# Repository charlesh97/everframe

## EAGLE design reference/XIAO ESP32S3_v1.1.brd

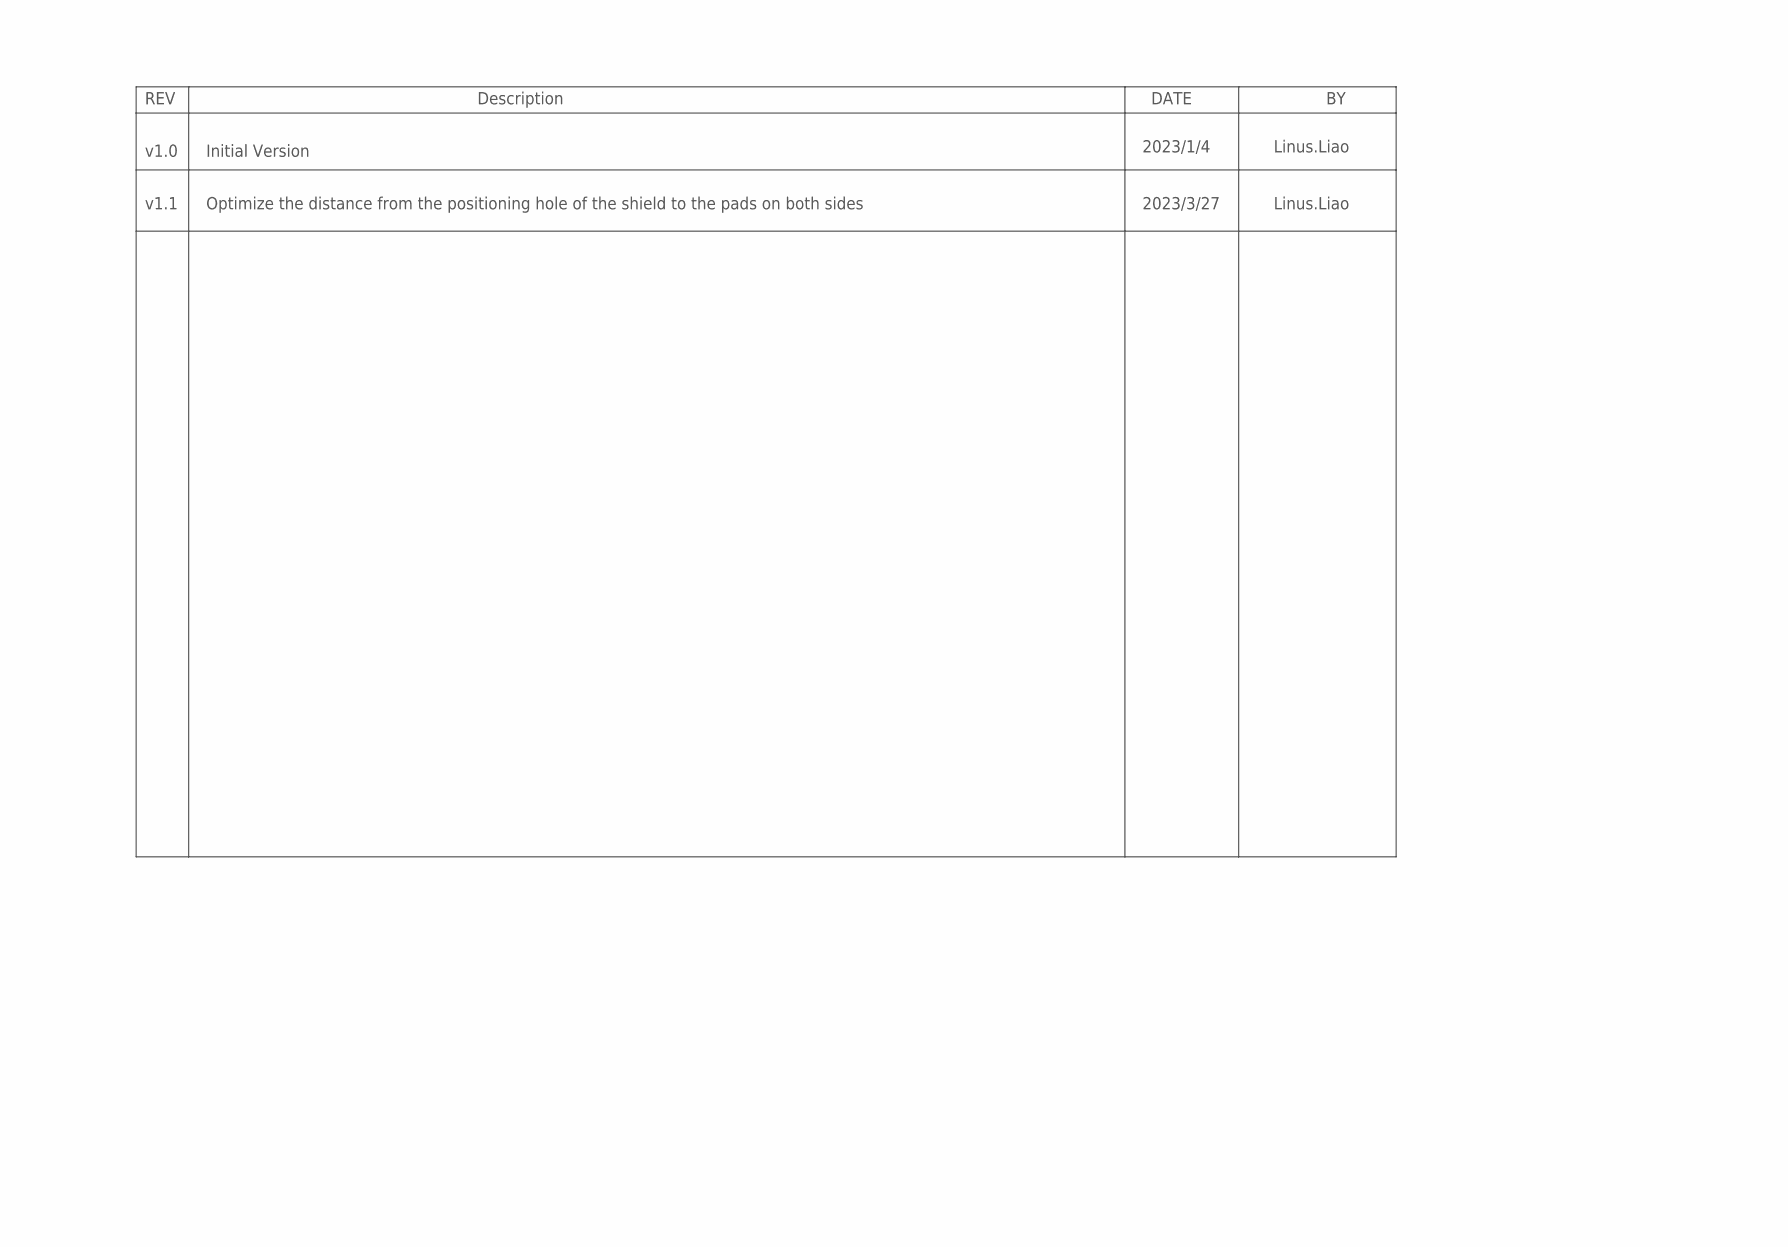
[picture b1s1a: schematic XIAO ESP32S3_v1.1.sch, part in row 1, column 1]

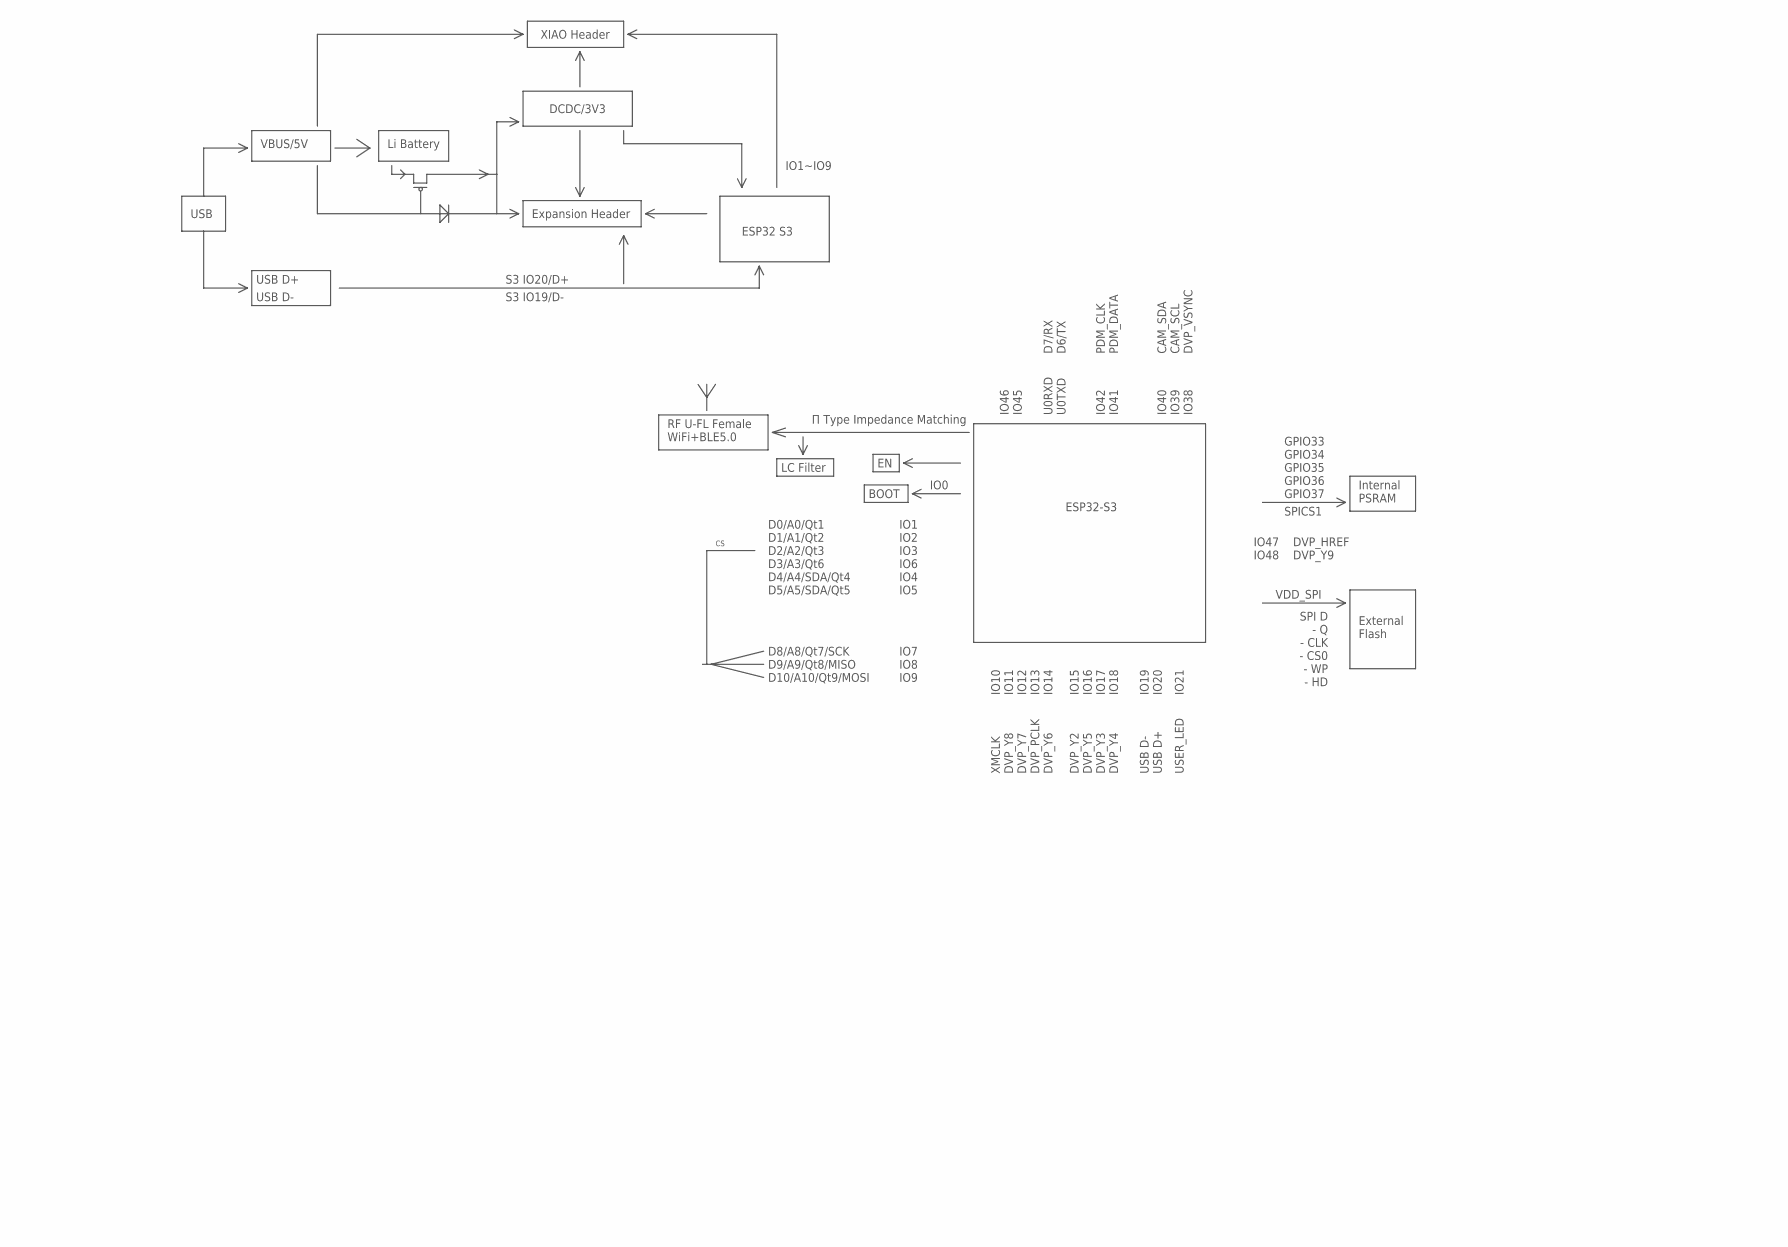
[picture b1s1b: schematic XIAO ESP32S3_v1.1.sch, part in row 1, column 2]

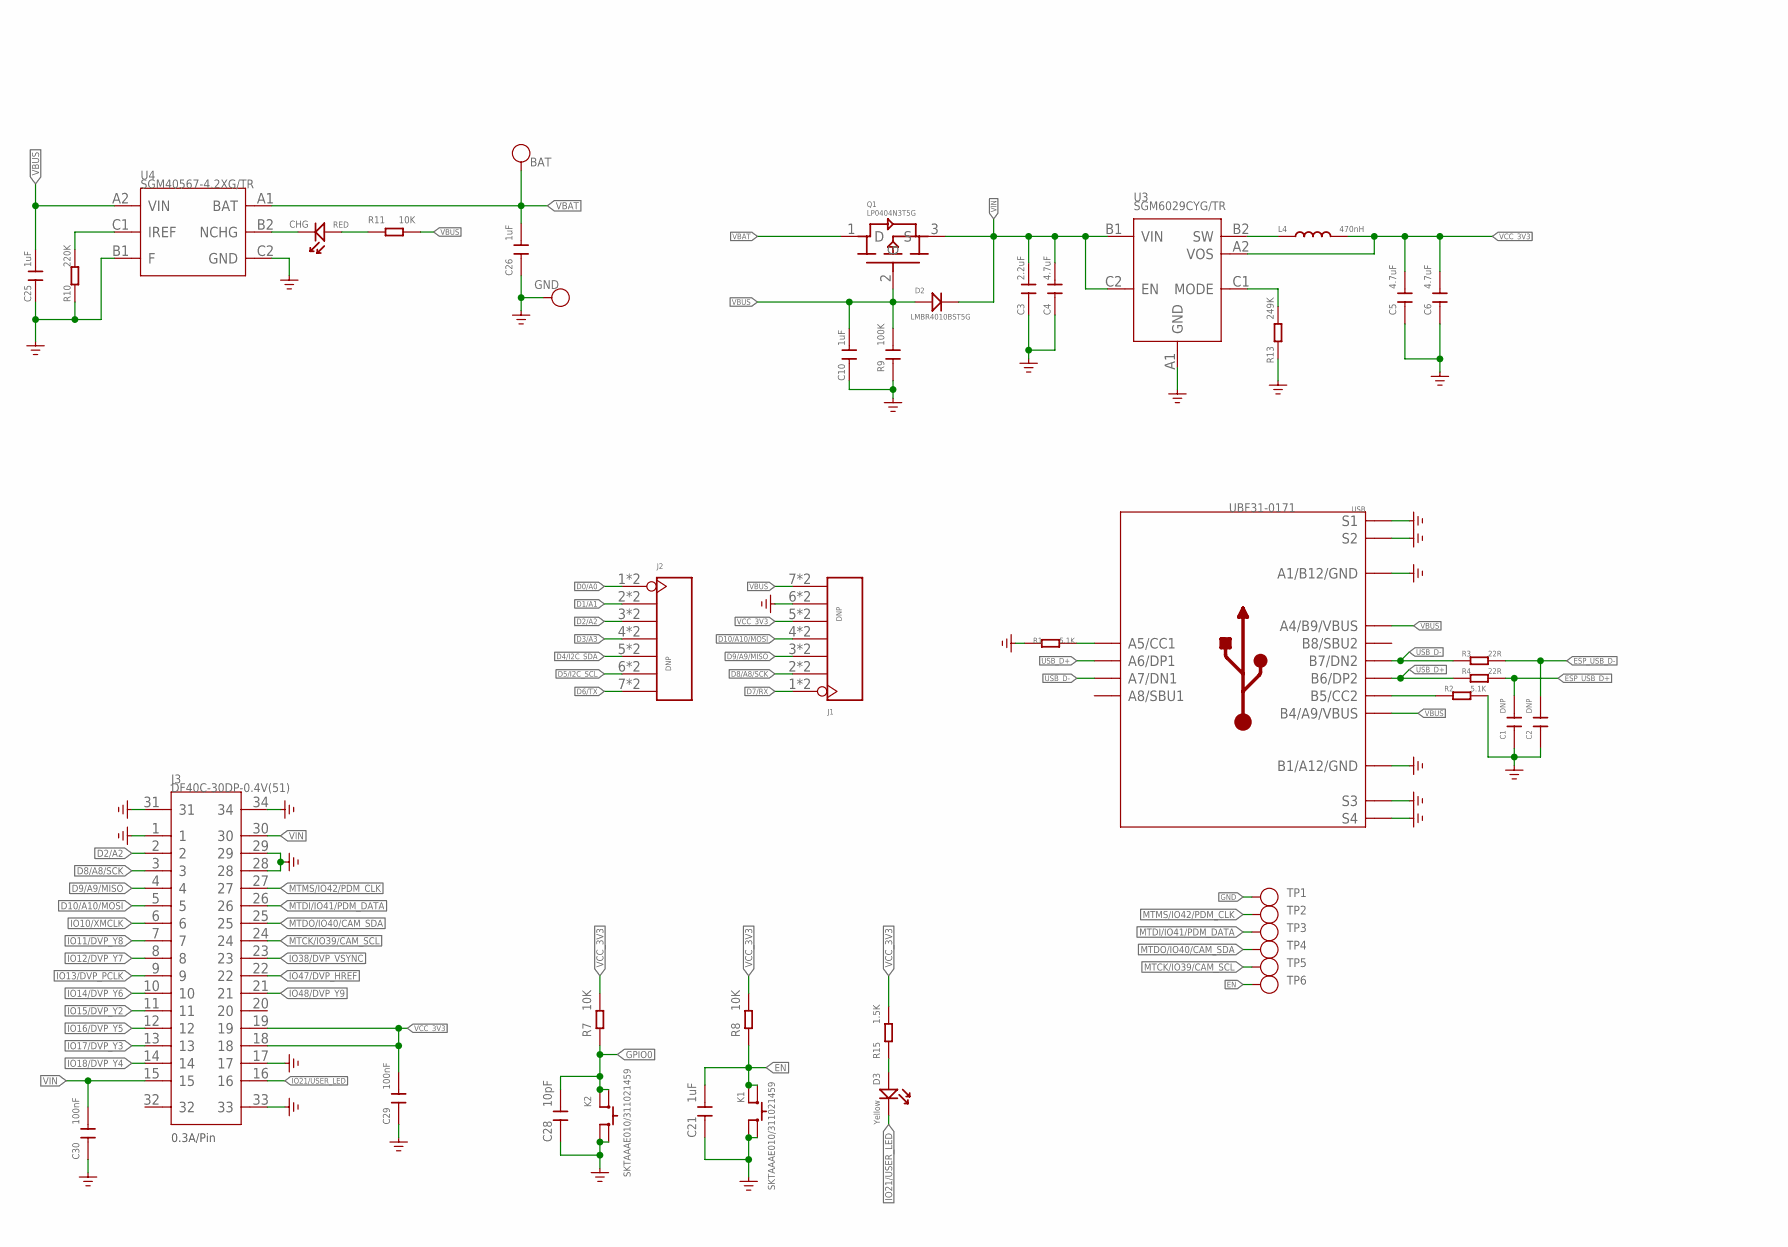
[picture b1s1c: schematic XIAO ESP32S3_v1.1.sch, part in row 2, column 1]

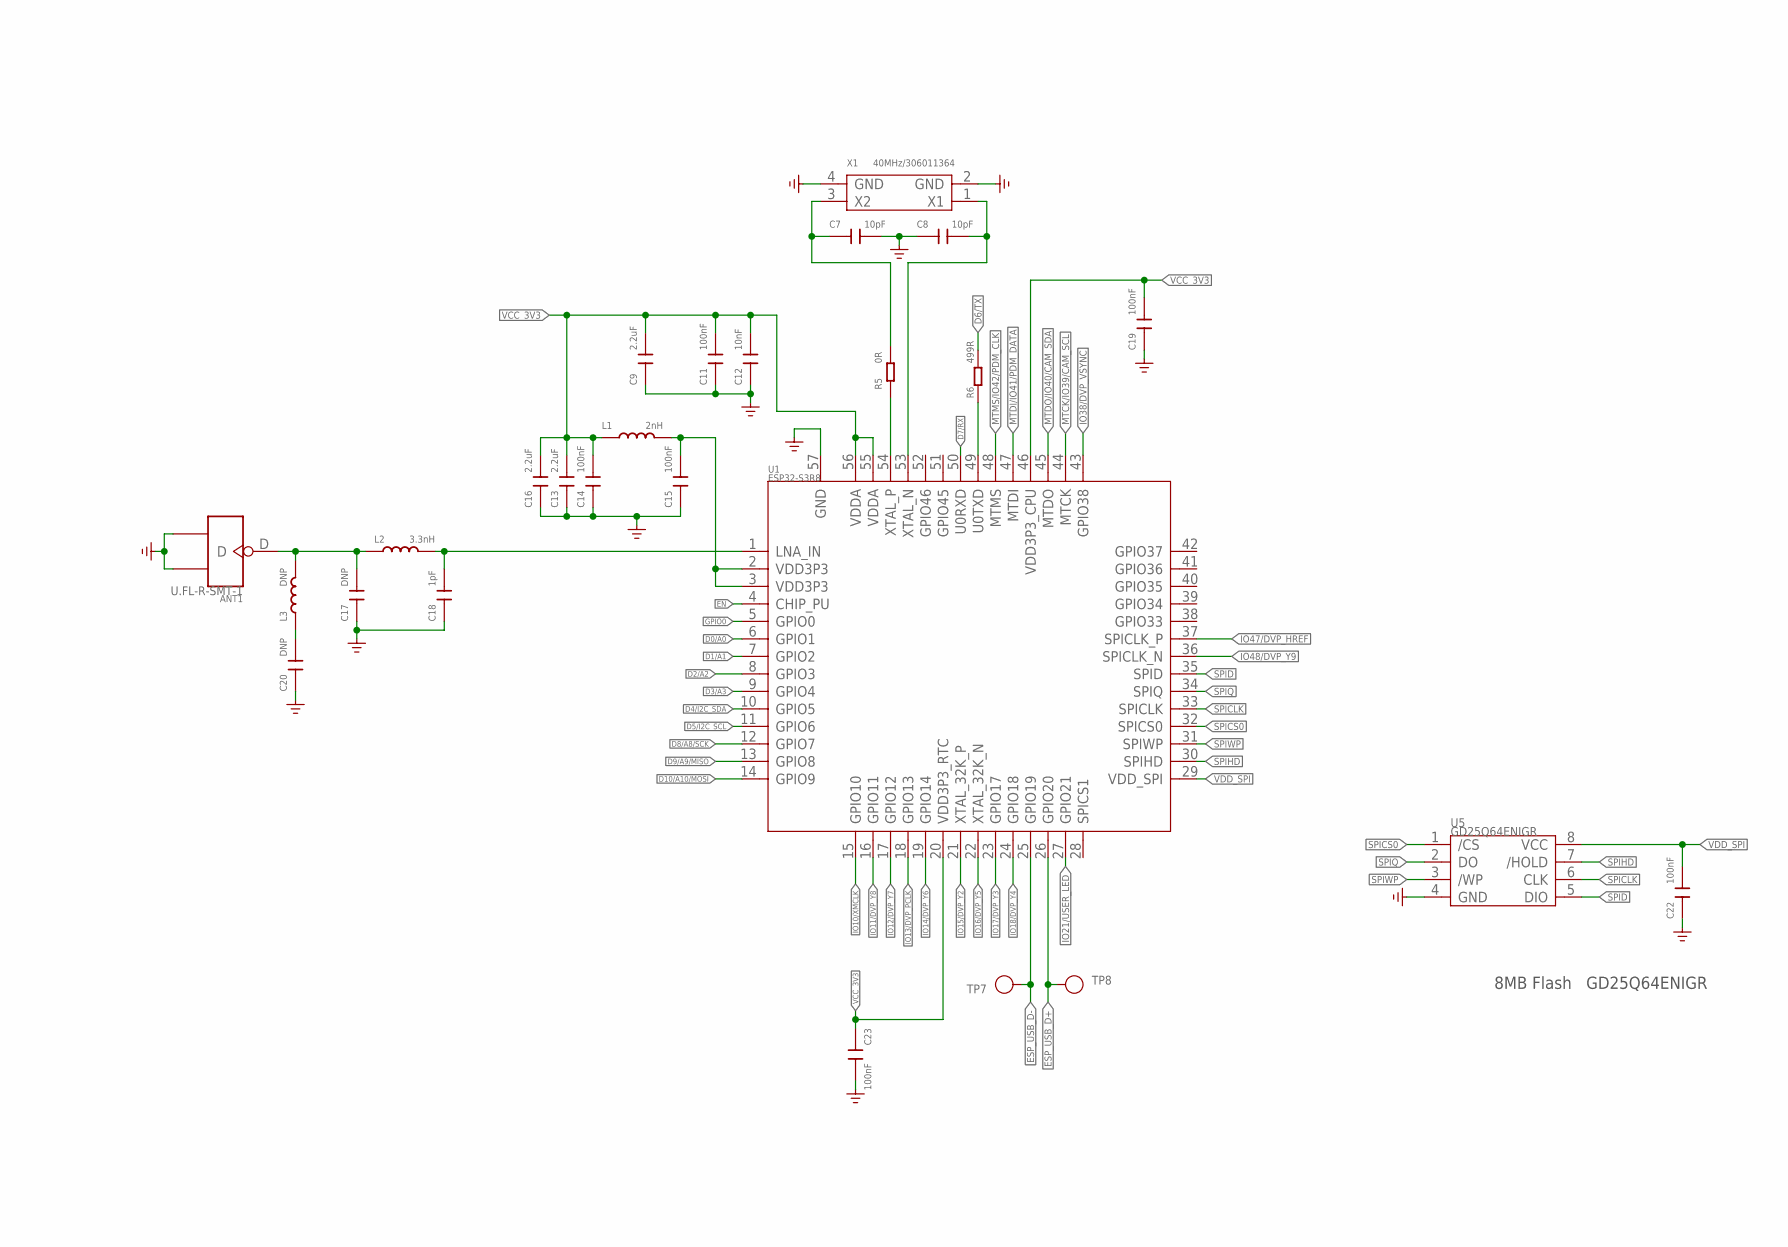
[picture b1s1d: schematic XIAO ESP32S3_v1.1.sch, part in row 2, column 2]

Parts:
ANT1: U.FL-R-SMT-1; U-FL3P-SMD-2.6X2.6X1.0MM
BAT: VBAT; TP-80X40MIL
C1, C2, C17, C20: DNP; C0201
C3, C9, C13, C16: 2.2uF; C0201
C4, C5, C6: 4.7uF; C0201
C7, C8, C28: 10pF; C0201
C10, C21, C25, C26: 1uF; C0201
C11, C14, C15, C19, C22, C23, C29, C30: 100nF; C0201
C12: 10nF; C0201
C18: 1pF; C0201
CHG: RED; LED-0402
D2: LMBR4010BST5G; DFN1006-2L
D3: Yellow; LED-0402
GND: GND; TP-80X40MIL
J1, J2: DNP; H7-HALF-HOLE-2.54
J3: DF40C-30DP-0.4V(51); BTB30-0.4-7.52X2.97X1.14
K1, K2: SKTAAAE010/311021459; SW4-SMD-2.8-2.6X1.6X0.53MM
L1: 2nH; L0201
L2: 3.3nH; L0201
L3: DNP; L0201
L4: 470nH; L0603
Q1: LP0404N3T5G; PMOS_1.0*0.6*0.35MM
R1, R2: 5.1K; R0201
R3, R4: 22R; R0201
R5: 0R; R0201
R6: 499R; R0201
R7, R8, R11: 10K; R0201
R9: 100K; C0201
R10: 220K; R0201
R13: 249K; R0201
R15: 1.5K; R0201
TP1, TP2, TP3, TP4, TP5, TP6, TP7, TP8: TEST-POINT'4545'; TP-D45MIL
U1: ESP32-S3R8; QFN56G-0.4-7X7MM
U3: SGM6029CYG/TR; BGA6-0.35-0.745X10.95X0.4MM
U4: SGM40567-4.2XG/TR; WLCSP-0.4-0.92X1.16X0.4MM
U5: GD25Q64ENIGR; USON8-0.8-4X3MM
USB: UBF31-0171; USB2.0-TYPE-C
X1: 40MHz/306011364; X4-SMD-1.6X1.2X0.35MM

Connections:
D0/A0: J2.1, J2.13 (1), U1.6 (GPIO1)
D1/A1: J2.2, J2.14 (2), U1.7 (GPIO2)
D2/A2: J2.3, J2.15 (3), J3.2, U1.8 (GPIO3)
D3/A3: J2.4, J2.16 (4), U1.9 (GPIO4)
D4/I2C_SDA: J2.5, J2.17 (5), U1.10 (GPIO5)
D5/I2C_SCL: J2.6, J2.18 (6), U1.11 (GPIO6)
D6/TX: J2.7, J2.19 (7), R6.2
D7/RX: J1.1, J1.13 (1), U1.50 (U0RXD)
D8/A8/SCK: J1.2, J1.14 (2), J3.3, U1.12 (GPIO7)
D9/A9/MISO: J1.3, J1.15 (3), J3.4, U1.13 (GPIO8)
D10/A10/MOSI: J1.4, J1.16 (4), J3.5, U1.14 (GPIO9)
EN: C21.2, K1.1 (A0), K1.3 (A1), R8.1, TP6.T, U1.4 (CHIP_PU)
ESP_USB_D+: C1.2, R4.2, TP8.T, U1.26 (GPIO20)
ESP_USB_D-: C2.2, R3.2, TP7.T, U1.25 (GPIO19)
GND: ANT1.GND1, ANT1.GND2, C1.1, C2.1, C3.2, C4.2, C5.1, C6.1, C7.2, C8.1, C9.1, C10.2, C11.1, C12.1, C13.1, C14.1, C15.1, C16.1, C17.1, C18.1, C19.1, C20.1, C21.1, C22.1, C23.2, C25.2, C26.2, C28.1, C29.1, C30.1, GND.1, J1.6, J1.18 (6), J3.1, J3.17, J3.28, J3.29, J3.31, J3.33, J3.34, K1.2 (B0), K1.4 (B1), K2.2 (B0), K2.4 (B1), R1.1, R2.2, R9.1, R10.1, R13.1, TP1.T, U1.57 (GND), U3.A1 (GND), U4.B1 (F), U4.C2 (GND), U5.4 (GND), USB.A1_B12 (A1/B12/GND), USB.B1_A12 (B1/A12/GND), USB.S1, USB.S2, USB.S3, USB.S4, USB.S5 (S1), USB.S6 (S2), X1.2 (GND), X1.4 (GND)
GPIO0: C28.2, K2.1 (A0), K2.3 (A1), R7.1, U1.5 (GPIO0)
IO10/XMCLK: J3.6, U1.15 (GPIO10)
IO11/DVP_Y8: J3.7, U1.16 (GPIO11)
IO12/DVP_Y7: J3.8, U1.17 (GPIO12)
IO13/DVP_PCLK: J3.9, U1.18 (GPIO13)
IO14/DVP_Y6: J3.10, U1.19 (GPIO14)
IO15/DVP_Y2: J3.11, U1.21 (XTAL_32K_P)
IO16/DVP_Y5: J3.12, U1.22 (XTAL_32K_N)
IO17/DVP_Y3: J3.13, U1.23 (GPIO17)
IO18/DVP_Y4: J3.14, U1.24 (GPIO18)
IO21/USER_LED: D3.-, J3.16, U1.27 (GPIO21)
IO38/DVP_VSYNC: J3.23, U1.43 (GPIO38)
IO47/DVP_HREF: J3.22, U1.37 (SPICLK_P)
IO48/DVP_Y9: J3.21, U1.36 (SPICLK_N)
MTCK/IO39/CAM_SCL: J3.24, TP5.T, U1.44 (MTCK)
MTDI/IO41/PDM_DATA: J3.26, TP3.T, U1.47 (MTDI)
MTDO/IO40/CAM_SDA: J3.25, TP4.T, U1.45 (MTDO)
MTMS/IO42/PDM_CLK: J3.27, TP2.T, U1.48 (MTMS)
unnamed: R5.1, U1.54 (XTAL_P)
unnamed: C7.1, R5.2, X1.3 (X2)
unnamed: C8.2, U1.53 (XTAL_N), X1.1 (X1)
unnamed: L4.1, U3.B2 (SW)
unnamed: ANT1.D, C17.2, L2.1, L3.2
unnamed: R2.1, USB.B5 (B5/CC2)
unnamed: C15.2, L1.2, U1.2 (VDD3P3), U1.3 (VDD3P3)
unnamed: R1.2, USB.A5 (A5/CC1)
unnamed: C18.2, L2.2, U1.1 (LNA_IN)
unnamed: CHG.-, U4.B2 (NCHG)
unnamed: R6.1, U1.49 (U0TXD)
unnamed: R10.2, U4.C1 (IREF)
unnamed: CHG.+, R11.2
unnamed: D3.+, R15.1
unnamed: R13.2, U3.C1 (MODE)
unnamed: C20.2, L3.1
SPICLK: U1.33 (SPICLK), U5.6 (CLK)
SPICS0: U1.32 (SPICS0), U5.1 (/CS)
SPID: U1.35 (SPID), U5.5 (DIO)
SPIHD: U1.30 (SPIHD), U5.7 (/HOLD)
SPIQ: U1.34 (SPIQ), U5.2 (DO)
SPIWP: U1.31 (SPIWP), U5.3 (/WP)
USB_D+: R4.1, USB.A6 (A6/DP1), USB.B6 (B6/DP2)
USB_D-: R3.1, USB.A7 (A7/DN1), USB.B7 (B7/DN2)
VBAT: BAT.1, C26.1, Q1.1 (D), U4.A1 (BAT)
VBUS: C10.1, C25.1, D2.+, J1.7, J1.19 (7), Q1.2 (G), R9.2, R11.1, U4.A2 (VIN), USB.A4_B9 (A4/B9/VBUS), USB.B4_A9 (B4/A9/VBUS)
VCC_3V3: C5.2, C6.2, C9.2, C11.2, C12.2, C13.2, C14.2, C16.2, C19.2, C23.1, C29.2, J1.5, J1.17 (5), J3.18, J3.19, L1.1, L4.2, R7.2, R8.2, R15.2, U1.20 (VDD3P3_RTC), U1.46 (VDD3P3_CPU), U1.55 (VDDA), U1.56 (VDDA), U3.A2 (VOS)
VDD_SPI: C22.2, U1.29 (VDD_SPI), U5.8 (VCC)
VIN: C3.1, C4.1, C30.2, D2.-, J3.15, J3.30, Q1.3 (S), U3.B1 (VIN), U3.C2 (EN)

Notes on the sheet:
v1.0
Initial Version
8MB Flash GD25Q64ENIGR
USB
VBUS/5V
USB D+
DCDC/3V3
XIAO Header
ESP32-S3
External Flash
VDD_SPI
SPI D - Q - CLK - CS0 - WP - HD
Internal PSRAM
GPIO33 GPIO34 GPIO35 GPIO36 GPIO37
RF U-FL Female WiFi+BLE5.0
Π Type Impedance Matching
LC Filter
BOOT
IO0
IO1
D0/A0/Qt1
D1/A1/Qt2
D2/A2/Qt3
D3/A3/Qt6
D4/A4/SDA/Qt4
D5/A5/SDA/Qt5
IO2
IO3
IO4
IO5
IO6
D6/TX
U0TXD
USB D-
IO19
IO20
D7/RX
D8/A8/Qt7/SCK
D9/A9/Qt8/MISO
D10/A10/Qt9/MOSI

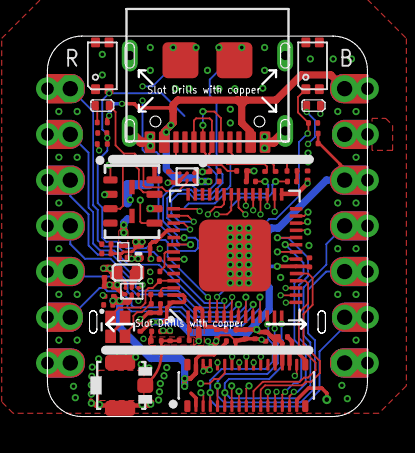
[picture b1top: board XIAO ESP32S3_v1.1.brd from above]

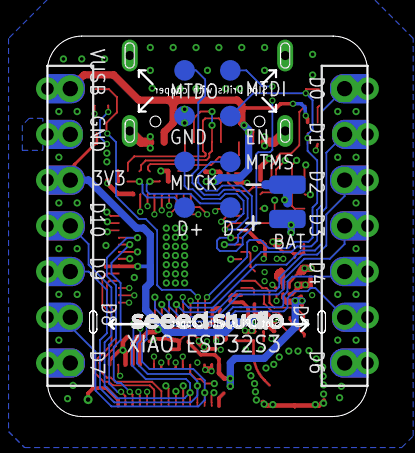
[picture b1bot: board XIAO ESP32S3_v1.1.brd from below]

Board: 4 copper layers, 17.8 x 21.1 mm, 72 parts (11 on the bottom side), 62 nets.

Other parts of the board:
U$7: LOGO-SEEED-NEW-0.94X8.4MM

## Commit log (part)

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2025-10-27 Starting up schematic and board files
2025-11-01 Finished sch, started layout 2L only
2025-11-03 Routed board, mostly need checks
2025-11-18 Update pcb and create packaging design
2025-11-28 Some unused google cloud function code added, esp32 idf embedded project added with display drivers, pcb fab exported
